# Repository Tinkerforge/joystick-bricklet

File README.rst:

Joystick Bricklet
=================

This repository contains the firmware source code and the hardware design
files. The documentation generator configs can be found at
https://github.com/Tinkerforge/generators

Repository Content
------------------

software/:
 * examples/: Examples for all supported languages
 * build/: Compiled files
 * src/: Source code of firmware
 * Makefile: Makefile to build project

hardware/:
 * Contains KiCad project files and additionally schematics as PDF

datasheets/:
 * Contains datasheets for sensors and complex ICs that are used

Hardware
--------

The hardware is designed with the open source EDA Suite KiCad
(http://www.kicad.org). Before you are able to open the files,
you have to install the Tinkerforge kicad-libraries
(https://github.com/Tinkerforge/kicad-libraries). You can either clone
them directly in hardware/ or clone them in a separate folder and
symlink them into hardware/
(ln -s kicad_path/kicad-libraries project_path/hardware). After that you
can open the .pro file in hardware/ with KiCad and from there view and
modify the schematics and the PCB layout.

Software
--------

If you want to do your own Brick/Bricklet firmware development we highly
recommend that you use our build environment setup script and read the
tutorial (https://www.tinkerforge.com/en/doc/Tutorials/Tutorial_Build_Environment/Tutorial.html).

To compile the C code we recommend you to install the newest GNU Arm Embedded
Toolchain (https://launchpad.net/gcc-arm-embedded/+download).
You also need to install bricklib (https://github.com/Tinkerforge/bricklib)
and brickletlib (https://github.com/Tinkerforge/brickletlib).

You can either clone it directly in software/src/ or clone it in a
separate folder and symlink it into software/src/
(ln -s bricklib_path/bricklib project_path/software/src/ and
ln -s brickletlib_path/brickletlib project_path/software/src/).
Finally make sure to have CMake installed
(http://www.cmake.org/cmake/resources/software.html).

After that you can build the firmware by invoking make in software/.
The firmware (.bin) can then be found in software/build/ and uploaded
with brickv (click button "Flashing" on start screen).

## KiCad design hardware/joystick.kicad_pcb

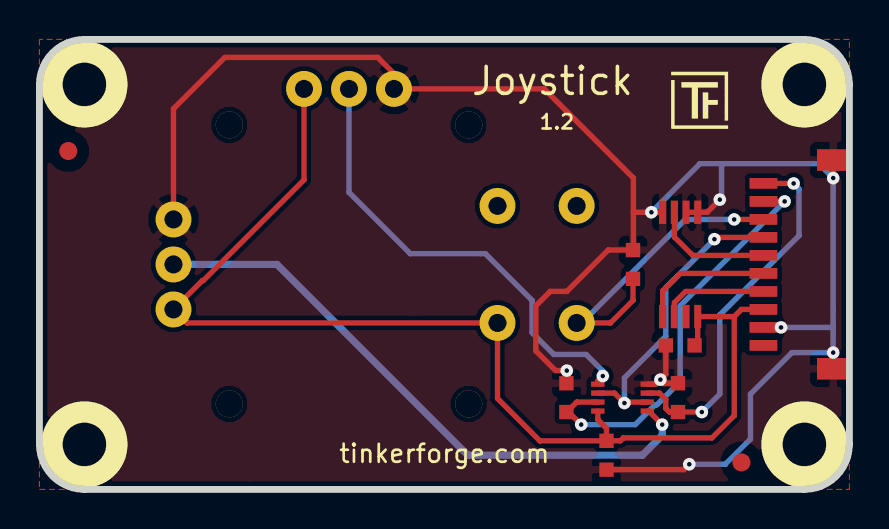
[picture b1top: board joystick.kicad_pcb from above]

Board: 2 copper layers, 45.0 x 25.0 mm, 18 parts (0 on the bottom side), 11 nets.

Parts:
C1: 100nF; C0603
C2: 1µF; C0603
Fiducial_Mark: VAL**; Fiducial_Mark
Fiducial_Mark#2: VAL**; Fiducial_Mark
P1: CON-SENSOR
R1, R2, R3: 10k; R0603
Ref**: Val**; Logo_31x31
U1: M24C64; TSSOP8
U2: NC7WB66K8X; VSSOP8
U3: JOYSTICK_BUTTON; Joystick_Button
U4, U5, U6, U7: DRILL; DRILL_NP
VAL: CE_5mm
VAL#2: WEEE_7mm

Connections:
A1: P1.9, R2.1, U2.7
A2: P1.10, R1.1, U2.3
GND: C1.1, C2.1, P1.2, P1.EP, R1.2, R2.2, R3.2, U1.1, U1.2, U1.4, U2.4, U3.X3, U3.Y3
IN_1: P1.7, U2.2, U2.6
unnamed: P1.6, U1.3
SCL: P1.4, U1.6
SDA: P1.5, U1.5
SWITCH: P1.8, R3.1, U3.SW2
VCC: C1.2, C2.2, P1.3, U1.8, U2.8, U3.SW1, U3.X1, U3.Y1
X: U2.5, U3.X2
Y: U2.1, U3.Y2

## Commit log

2011-08-25 initial hardware source commit
2011-08-25 add project description
2011-08-26 remove debug output
2011-09-05 Remove offset because of better optimization in newer gccs
2011-09-13 add java bindings and examples
2011-09-14 limit line length of java examples to 100 characters
2011-09-23 Add C# examples and bindings
2011-10-05 Remove Bindings and IP Connection (these are generated and they change too often) and rename bindings to examples
2011-10-05 add tinkerforge package to python imports
2011-10-06 remove faulty gcc commandline invocation
2011-10-06 add firmware version and name
2012-02-13 check in of version V1.1: - remove address line resistor - board: add fiducial markers
2012-02-14 add compatability for different tick types
2012-02-15 Add changelog
2012-02-15 Move software changelog to software folder
2012-02-24 use O2 instead of O3, firmware is too big otherwise
2012-03-09 Add sleep time between joystick direction change (otherwise analog switch sometimes gets hot)
2012-03-09 Use 16bit for joystick calibration (8 bit to small for some joysticks)
2012-04-25 Unify capitalization of "IP connection" in examples
2012-05-09 Add PHP examples
2012-05-14 java: Remove unnecessary new String(...) calls
2012-05-25 Add Ruby examples
2012-06-01 Use correct bool logic for "outside callback"
2012-06-05 Fix register_callback syntax error in Ruby examples on Windows
2012-06-12 Use correct term 'Bricklet' in example code error message
2012-06-12 Prefer IPConnection destroy over join_thread
2012-06-21 Fix threshold period error (missing parentheses)
2012-07-01 Add generate_makefile.bat for windows
2012-07-25 Add Delphi examples
2012-08-08 delphi: Add comment about UID
2012-10-24 Make cmake find the correct objcopy binary
    On some systems cmake uses the wrong objcopy binary, tell it to use
    the correct one.
2012-11-13 Support for protocol 2.0
2012-11-27 Remove unnecesary debug output
2012-11-29 Make examples compatible to Protocol V2.0
2012-11-29 Make Ruby examples Protocol 2.0 compatible
2012-11-29 Make C examples Protocol 2.0 compatible
2012-11-29 Make Java examples Protocol 2.0 compatible
2012-11-29 Make PHP examples Protocol 2.0 compatible
2012-11-29 Make Delphi/Pascal examples Protocol 2.0 compatible
2012-11-30 delphi: Remove unnecessary parentheses and call destructor again
2012-12-05 Add protocol 2.0 compatability to C# bindings
2012-12-06 Fix C examples
2012-12-11 Avoid g++ warnings about missing casts in C examples
2012-12-21 Add .gitignore
2013-01-09 Use specific device object for callbacks
2013-01-15 Turn debug output off
2013-01-17 Make Java examples compatible to new listener approach
2013-01-28 Update outdated comment in Java example
2013-01-28 Fix timeout in threshold callback functions (through brickletlib)
2013-01-28 Adapt Find Corners examples to behavior change of outside callback
2013-02-07 Use IPconnection disconnect explicitly in examples
2013-02-13 Add missing ReadKey call to C# example
2013-02-14 Increase analog value integration time (through brickletlib) and decrease averaging to allow more stable joystick values if Joystick is used over WiFi
2013-02-18 Add Visual Basic .NET examples
2013-08-12 Add shell examples
2013-08-12 shell: Add note to example
2013-08-21 windows: Don't trigger a build in generate_makefile.bat
    Also use normal make instead of a special named one.
2013-09-19 Example to fake mouse movement and clicks on windows
2013-09-20 c: Ensure that the mouse example compiles on non-Windows too
2013-12-19 Fix wrong length for GetDebounce packet (through brickletlib)
2014-01-06 Add static assert for BrickContext size
2014-01-10 Add Perl examples
2014-01-15 php: Use const for constant values
2014-02-07 Add Mathematica examples
2014-02-10 perl: fixed namespace
2014-02-11 javascript: add examples
2014-02-18 javascript: examples fixed
2014-02-20 javascript: add html examples
2014-02-24 javascript: port 4280, startExample()
2014-02-28 javascript: Break long lines and cleanup whitespace
2014-03-05 Add LabVIEW examples
2014-03-06 labview: Add examples in LV2010 format
2014-03-25 matlab: add examples
2014-04-02 java: Unify constants style
2014-04-02 perl: Unify print style
2014-04-17 matlab: Adapt examples to new callback style
2014-04-17 matlab: Add parentheses to make pygments happy
2014-04-17 matlab: Fix string in Octave
2014-07-15 java: Replace System.console() usage with an Eclipse compatible pattern
2014-12-02 Use ReadLine instead of ReadKey for C# example
2015-02-13 vbnet: Use ReadLine instead of ReadKey
    Because ReadKey doesn't work with a pipe as stdin on the RED Brick.
2015-03-02 windows: Stop cmake from searching for mingw32-make.exe
    Using MinGW Makefiles as generator makes cmake search for mingw32-make.exe
    which might not be installed because GnuWin32's make.exe is used instead.
2015-03-26 update to latest hardware files
2015-04-09 c: Whitespace
2015-06-24 javascript: Clean up output creation
2015-06-29 octave: Handle short difference between Octave 3.6 and 3.8
    In Octave 3.6 a short is not autoamtically handled as a number.
2015-07-03 drc rulecheck run
2015-07-08 add missing hardware file
2015-07-23 Make JavaScript browser example textarea readonly
2015-07-27 Cleanup C/C++, C#, Java, Python and Ruby examples
2015-07-27 Whitespace
2015-07-28 Add missing import in Java example
2015-07-29 Reformat changelog
2015-08-07 Use full device class name in Python examples
2015-08-12 Fix minor warnings in C/C++ examples
2015-08-17 Cleanup Delphi examples
2015-08-18 Cleanup VB.NET examples
2015-08-19 Cleanup Perl examples
2015-09-09 Duplicate cmake call to fix bug during cmake creation
2015-09-15 shell: Fix example name
2015-09-15 c: Cleanup Windows mouse example
2015-09-30 Generator based example cleanup
2015-11-12 matlab: Fix callback handling for R2014a
    http://undocumentedmatlab.com/blog/matlab-callbacks-for-java-events-in-r2014a
2015-11-25 Include date and commit into changelog
2015-11-30 vbnet: Shorten long lines
2016-05-18 c: Add missing device destroy call
2016-07-01 Make the change UID comment more explicit
2017-04-13 csharp: Adapt example
2017-04-21 shell: Adapt example
2017-06-02 octave: Use javaObject instead of deprecated java_new
2017-11-30 Update examples from generator
2017-12-07 mathematica: Also generate .nb files
2018-02-02 Update examples
2018-02-19 javascript: Close div tag correctly
2018-02-20 Cleanup KiCad libraries config
    Ensure LibDir=kicad-libraries and LibName1=tinkerforge.
    Remove special library.
2018-05-24 perl: Use strict in examples
2018-05-28 mathematica: Reorder some lines for clearity
2018-07-06 Add 3d information
2018-07-06 Add 3d model (*.FCStd & *.step)
2018-07-11 Add Makefile with docker support
2018-07-11 Update directory structure and build instructions
2018-07-11 Remove obsolete generate_makefile scripts
2018-11-06 Add rust examples
2018-11-07 rust: Accept host names for ip connection, fix naming inconsistencies
2018-11-07 rust: Rename callback receivers.
2018-12-14 Add go examples.
2018-12-18 go: Change import path.
2018-12-18 go: Change import path again.
2018-12-20 rust: Fix result variable names in examples.
2018-12-20 rust: Reformat examples.
2019-01-24 mqtt: Add examples.
2019-01-24 mqtt: Fix example header.
2019-01-24 mqtt: Remove executable bit in example permissions.
2019-01-24 go: Minor example fixes.
2019-01-24 mqtt: Minor example fixes.
2019-03-28 mqtt: Fix whitespace.
2019-05-14 Update rust examples.
2019-08-22 c: Adapt to bindings changes
2020-01-13 examples: Use python3 input instead of python2 raw_input.
2020-01-13 examples: mqtt: Remove trailing whitespace.
2020-01-14 examples: Use python3 input by default.
2020-02-26 c: Update "Change UID" comment style
2020-03-18 mqtt: Fix x/y print logic
2020-03-18 rust: Update to new skeleton
2021-10-25 Update KiCad link
    https://www.kicad.org/blog/2021/10/Avoid-links-to-former-kicad-domain/
2022-05-10 go: Fix format string
2022-07-06 Add license files.

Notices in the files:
hardware/joystick.kicad_pcb:
Licensed under CERN OHL v.1.1
Copyright (©) 2011, B.Nordmeyer
Copyright Tinkerforge GmbH 2011.
This documentation describes Open Hardware and is licensed under the
CERN OHL v. 1.1.
